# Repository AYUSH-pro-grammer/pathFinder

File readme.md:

# Pathfinder – Tiny Reaction Game!

Hello!! 
This is my Hack Club Stasis project  its based on reaction time and a bit of fun

---

## How It Works

- LEDs blink
- You press buttons 
- Turn the knob
- Try to react FAST!!

### Rules:
- Press button 1 -> led 1 lights up 
- Press button 2 -> quickly after btn1 -> builds combo both will get on
- if you press button 2 quickly and multiple times then led2 turns on
- Too slow? nothing happens

---

## Images

### 3D View

### Circuit

### Schematic

---

## Components

- LEDs 
- Resistors 
- Xiao RP2040 
- Cherry MX switches 
- PCB 
- Potentiometer (knob!!) 

---

## Code

```cpp
int btn1 = D0;
int btn2 = D1;
int led1 = D2;
int led2 = D3;

int potentio = D4;

long btn2cnt = 0;
long button1time = 0;
long button2time = 0;

void setup() {
  pinMode(btn1, INPUT_PULLUP);
  pinMode(btn2, INPUT_PULLUP);
  pinMode(potentio, INPUT);

  pinMode(led1, OUTPUT);
  pinMode(led2, OUTPUT);
}

void loop() {

  int pot_reading = analogRead(potentio);
  int brightness = map(pot_reading, 0, 1023, 0, 255);

  if (digitalRead(btn1) == LOW) {
    button1time = millis();
    analogWrite(led1, brightness);
  } else {
    analogWrite(led1, 0);
  }

  if (digitalRead(btn2) == LOW) {
    button2time = millis();
    btn2cnt += 1;
  }

  if (abs(button1time - button2time) <= 1000) {
    if (btn2cnt > 2) {
      analogWrite(led2, brightness);
      btn2cnt = 0;
    }
  } else {
    analogWrite(led2, 0);
  }
}

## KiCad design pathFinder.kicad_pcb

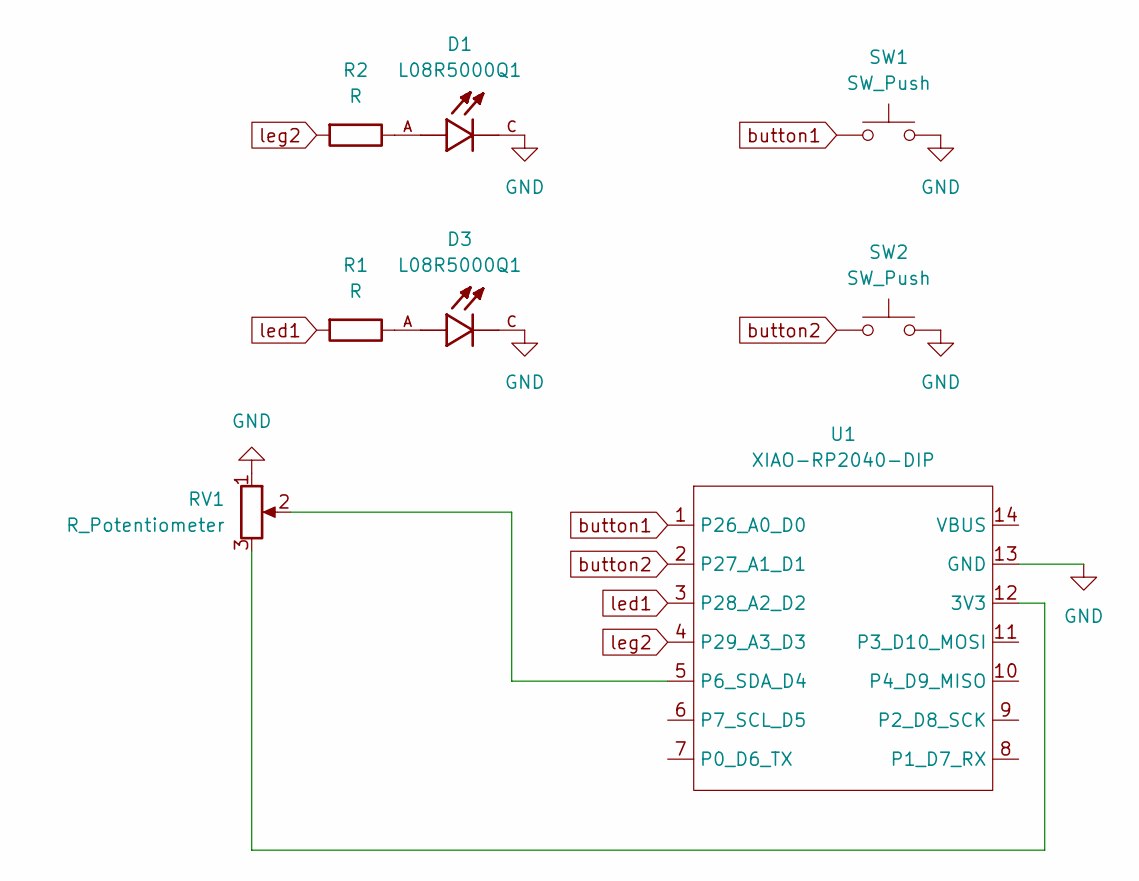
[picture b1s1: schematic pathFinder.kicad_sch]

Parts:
D1, D3: L08R5000Q1; LEDRD254W57D500H1070; PARTREV NA
R1, R2: R; R_Axial_DIN0204_L3.6mm_D1.6mm_P5.08mm_Horizontal
RV1: R_Potentiometer; Potentiometer_Alps_RK09K_Single_Vertical
SW1, SW2: SW_Push; SW_Cherry_MX_1.00u_PCB
U1: XIAO-RP2040-DIP

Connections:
GND: D1.C, D3.C, RV1.1, SW1.2, SW2.2, U1.13 (GND)
unnamed: D1.A, R2.1
unnamed: D3.A, R1.1
unnamed: RV1.3, U1.12 (3V3)
unnamed: RV1.2, U1.5 (P6_SDA_D4)
button1: SW1.1, U1.1 (P26_A0_D0)
button2: SW2.1, U1.2 (P27_A1_D1)
led1: R1.2, U1.3 (P28_A2_D2)
leg2: R2.2, U1.4 (P29_A3_D3)

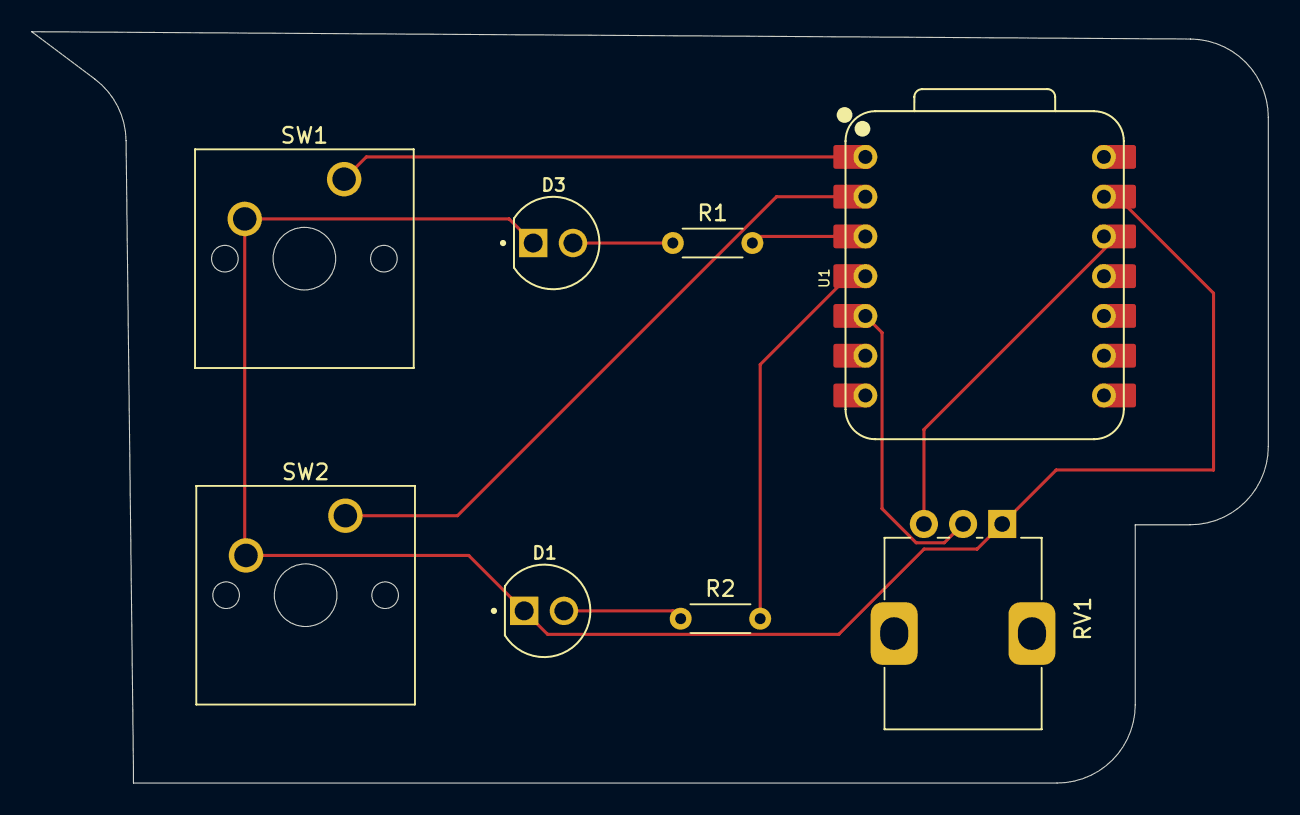
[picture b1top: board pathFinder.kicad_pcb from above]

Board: 2 copper layers, 79.0 x 48.0 mm, 8 parts (0 on the bottom side), 9 nets.

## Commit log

2026-04-04 added files
2026-04-09 pushed
2026-04-09 minor
